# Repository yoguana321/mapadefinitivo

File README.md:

# APP MiUnal - GPS
Proyecto de Introduccion y Taller de ingeniería electrónica - UNAL - 2025-1

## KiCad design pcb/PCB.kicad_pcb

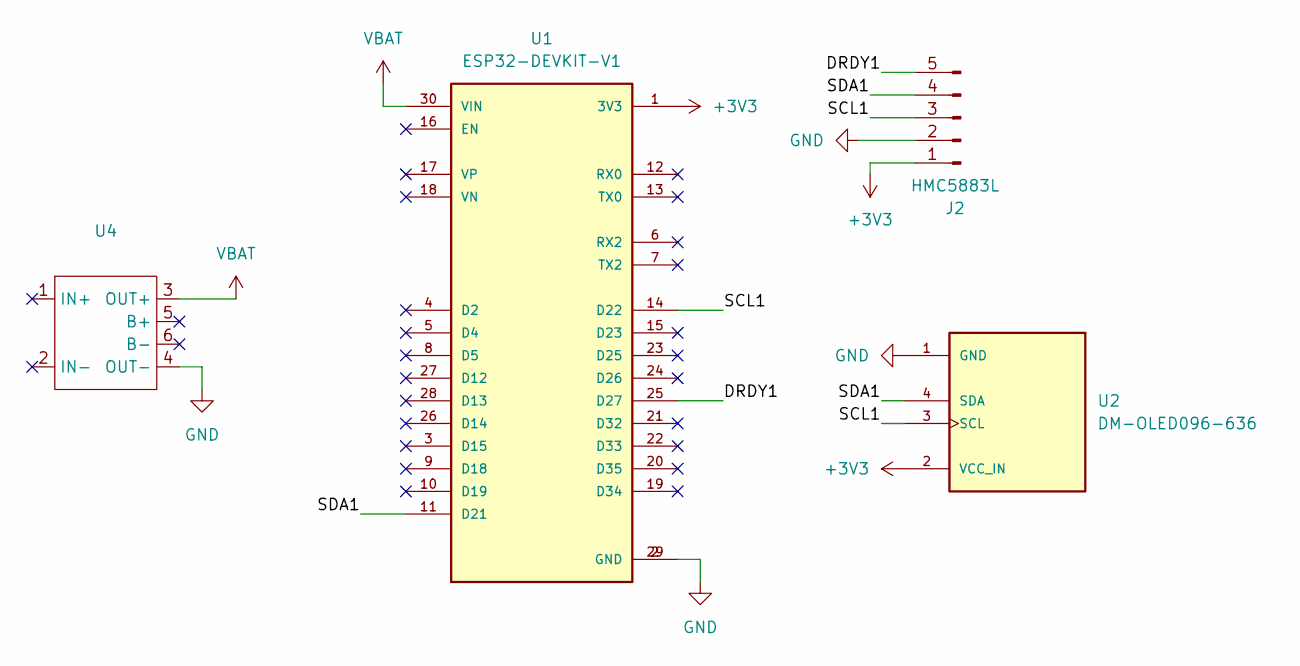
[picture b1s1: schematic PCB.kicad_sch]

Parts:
J2: HMC5883L; PinHeader_1x05_P2.54mm_Vertical
U1: ESP32-DEVKIT-V1; MODULE_ESP32_DEVKIT_V1; PARTREV N/A
U2: DM-OLED096-636; MODULE_DM-OLED096-636; PARTREV 2018-09-10
U4: TP4056 Li-Ion Charger; TP4056-Module

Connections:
+3V3: J2.1, U1.1 (3V3), U2.2 (VCC_IN)
/DRDY1: J2.5, U1.25 (D27)
/SCL1: J2.3, U1.14 (D22), U2.3 (SCL)
/SDA1: J2.4, U1.11 (D21), U2.4 (SDA)
GND: J2.2, U1.2 (GND), U1.29 (GND), U2.1 (GND), U4.4 (OUT-)
VBAT: U1.30 (VIN), U4.3 (OUT+)

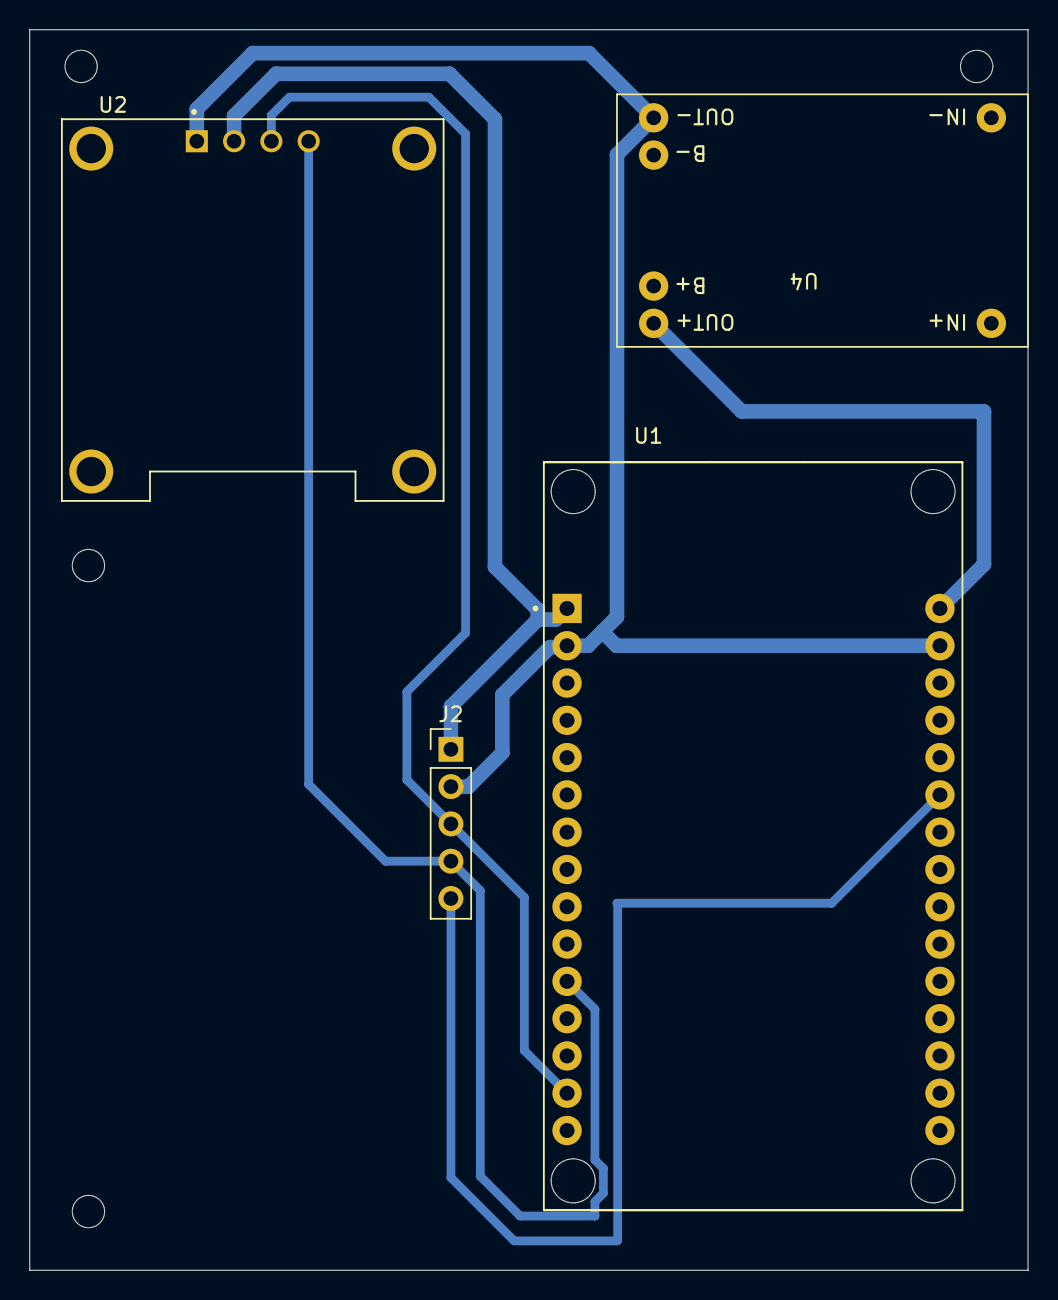
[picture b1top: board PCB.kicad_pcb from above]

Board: 2 copper layers, 68.0 x 84.5 mm, 4 parts (0 on the bottom side), 6 nets.

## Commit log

2025-06-18 Primer commit del proyecto Mapadefinitivo
2025-06-19 Subida inicial de app Flutter
2025-06-20 arreglar el screen para la foking interfaz
2025-06-21 Brujula y mejoras de interfaz
2025-07-01 Funcion Favoritos
2025-07-02 arreglar la info de los markers
2025-07-06 PuntoGPS
2025-07-07 Routing_Service y Boton ir alla
2025-07-07 Actualización bugs GPS
2025-07-08 corregir/mejorar informacion markers
2025-07-08 añadir y mejorar la info de los edificios
2025-07-09 BUG GPS
2025-07-11 Logo,SplashScreen,Brujula,ModoOscuro,BotonIrReubicado
2025-07-12 añadir y mejorar la info de los edificios- reworkeado falta la info
2025-07-14 Create TALLER
2025-07-14 Create pcb
2025-07-14 Agregar archivos de la pcb
    _pcd, _sch, .step
2025-07-20 mas rework falta
2025-07-22 filtrado mejor y salidas (y la bicirun) faltan ah y imagenes
2025-07-22 modificable
2025-07-22 final gelves
2025-07-22 Как я ненавижу знакомство
2025-07-22 nuevo
